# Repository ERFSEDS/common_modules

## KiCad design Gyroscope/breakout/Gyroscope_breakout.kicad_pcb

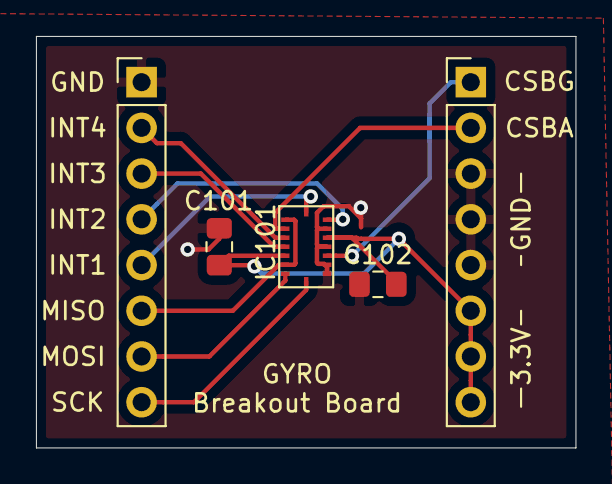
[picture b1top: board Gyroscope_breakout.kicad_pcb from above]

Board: 2 copper layers, 30.0 x 22.9 mm, 5 parts (0 on the bottom side), 11 nets.

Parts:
C101, C102: 100nF; C_0805_2012Metric_Pad1.15x1.40mm_HandSolder
IC101: BMI088; 16-LGA-(4.5x3)
J101: Conn_01x08; PinHeader_1x08_P2.54mm_Vertical
e101: Conn_01x08; PinHeader_1x08_P2.54mm_Vertical

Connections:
+3V3: C101.2, C102.2, IC101.3, IC101.11, e101.6, e101.7, e101.8
/CSB_ACCEL: IC101.14, e101.2
/CSB_GYRO: IC101.5, e101.1
/INT1_ACCEL: IC101.16, J101.5
/INT2_ACCEL: IC101.1, J101.4
/INT3_GYRO: IC101.12, J101.3
/INT4_GYRO: IC101.13, J101.2
/MISO: IC101.10, IC101.15, J101.6
/MOSI: IC101.9, J101.7
/SCK: IC101.8, J101.8
GND: C101.1, C102.1, IC101.2, IC101.4, IC101.6, IC101.7, J101.1, e101.3, e101.4, e101.5

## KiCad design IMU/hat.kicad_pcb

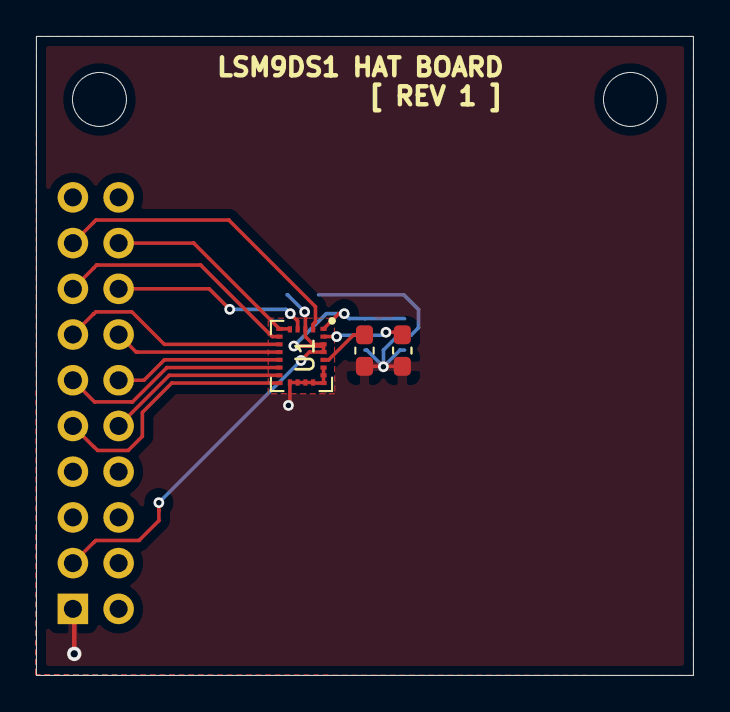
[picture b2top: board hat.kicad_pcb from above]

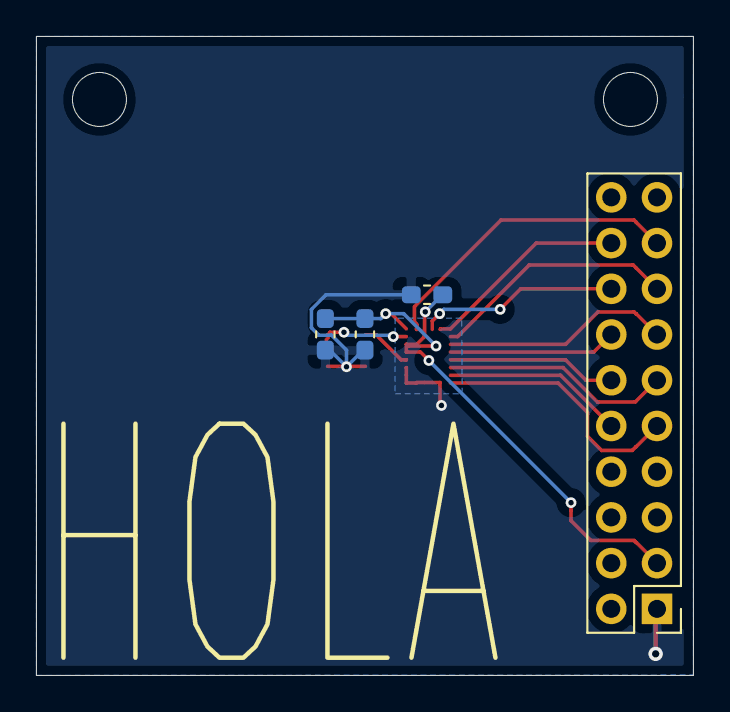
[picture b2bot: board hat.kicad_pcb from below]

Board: 2 copper layers, 36.5 x 35.5 mm, 9 parts (4 on the bottom side), 14 nets.

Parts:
C1: 10nF; C_0603_1608Metric_Pad1.05x0.95mm_HandSolder
C2, C3, C4: 100nF; C_0603_1608Metric_Pad1.05x0.95mm_HandSolder
C5: 10uF; C_0603_1608Metric_Pad1.05x0.95mm_HandSolder
H1, H3: MountingHole; MountingHole_3mm
J1: Conn_02x10_Odd_Even; PinHeader_2x10_P2.54mm_Vertical
U1: LSM9DS1; LGA-24L_3x3.5mm_P0.43mm

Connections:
+3V3: C2.1, C4.1, C5.1, J1.3, U1.1, U1.3, U1.22, U1.23
/CS: J1.15, U1.7
/CSM: J1.13, U1.8
/DEN: J1.9, U1.13
/DRDYM: J1.14, U1.9
/INT1: J1.11, U1.11
/INT2: J1.10, U1.12
/INTM: J1.12, U1.10
/MISO: J1.18, U1.5, U1.6
/MOSI: J1.16, U1.4
/SCLK: J1.17, U1.2
GND: C1.2, C2.2, C3.2, C4.2, C5.2, J1.1, U1.14, U1.15, U1.16, U1.17, U1.18, U1.19, U1.20
unnamed: C1.1, U1.21
unnamed: C3.1, U1.24

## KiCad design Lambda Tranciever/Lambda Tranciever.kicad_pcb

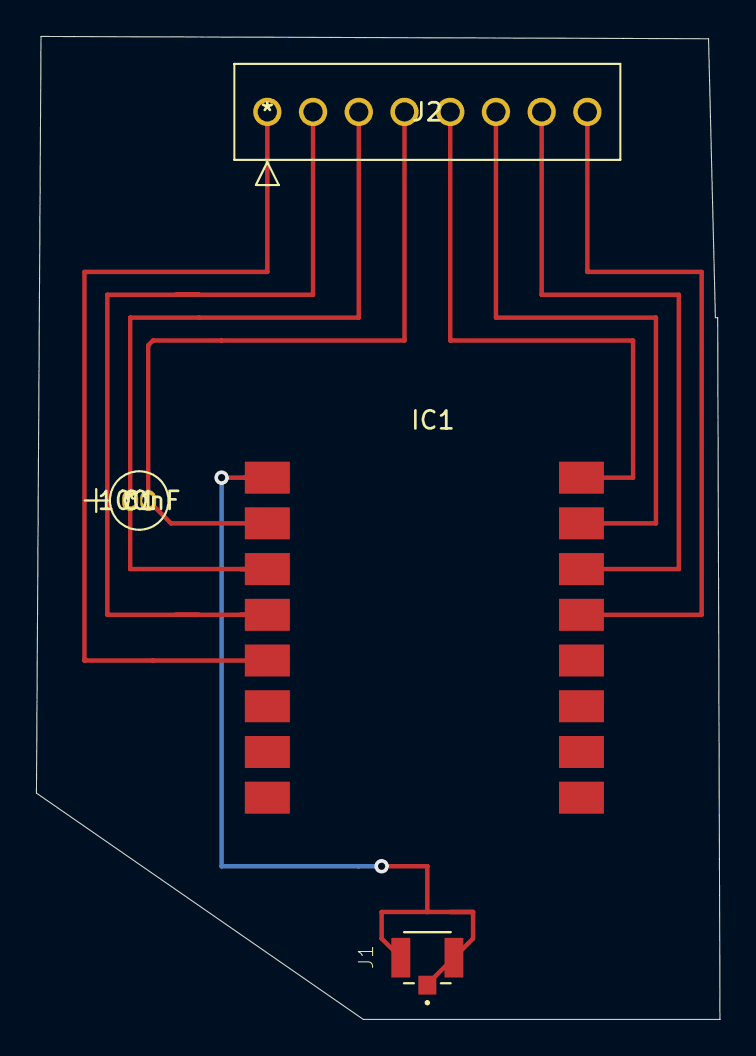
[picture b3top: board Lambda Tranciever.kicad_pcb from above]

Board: 2 copper layers, 38.0 x 54.6 mm, 4 parts (0 on the bottom side), 9 nets.

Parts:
C1: 100nF; UMA1H0R1MCD2TP
IC1: LAMBDA-9S
J1: U.FL-R-SMT(10); HRS_U.FL-R-SMT(10)
J2: PPTC081LFBN-RC

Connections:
+3V3: C1.1, IC1.3, J2.3
/12(RX2): IC1.5, J2.1
/13(TX2): IC1.4, J2.2
/19(SS): IC1.16, J2.5
/20(SCK): IC1.13, J2.8
/21(MOSI): IC1.15, J2.6
/22(MISO): IC1.14, J2.7
GND: C1.2, IC1.2, J2.4
unnamed: IC1.1, J1.1, J1.2, J1.3

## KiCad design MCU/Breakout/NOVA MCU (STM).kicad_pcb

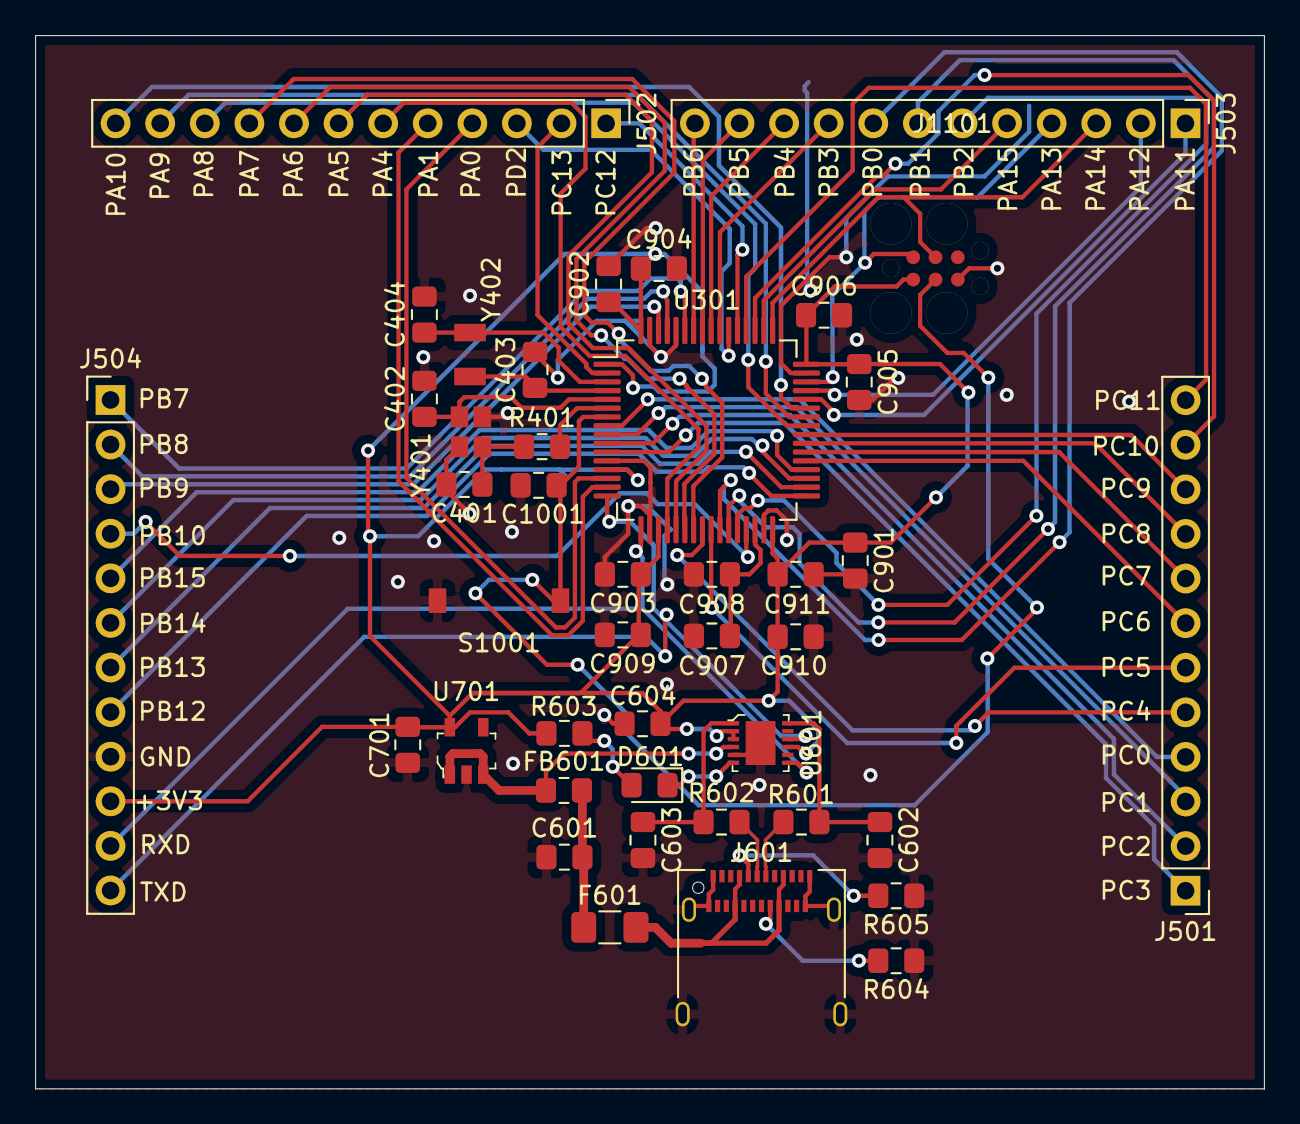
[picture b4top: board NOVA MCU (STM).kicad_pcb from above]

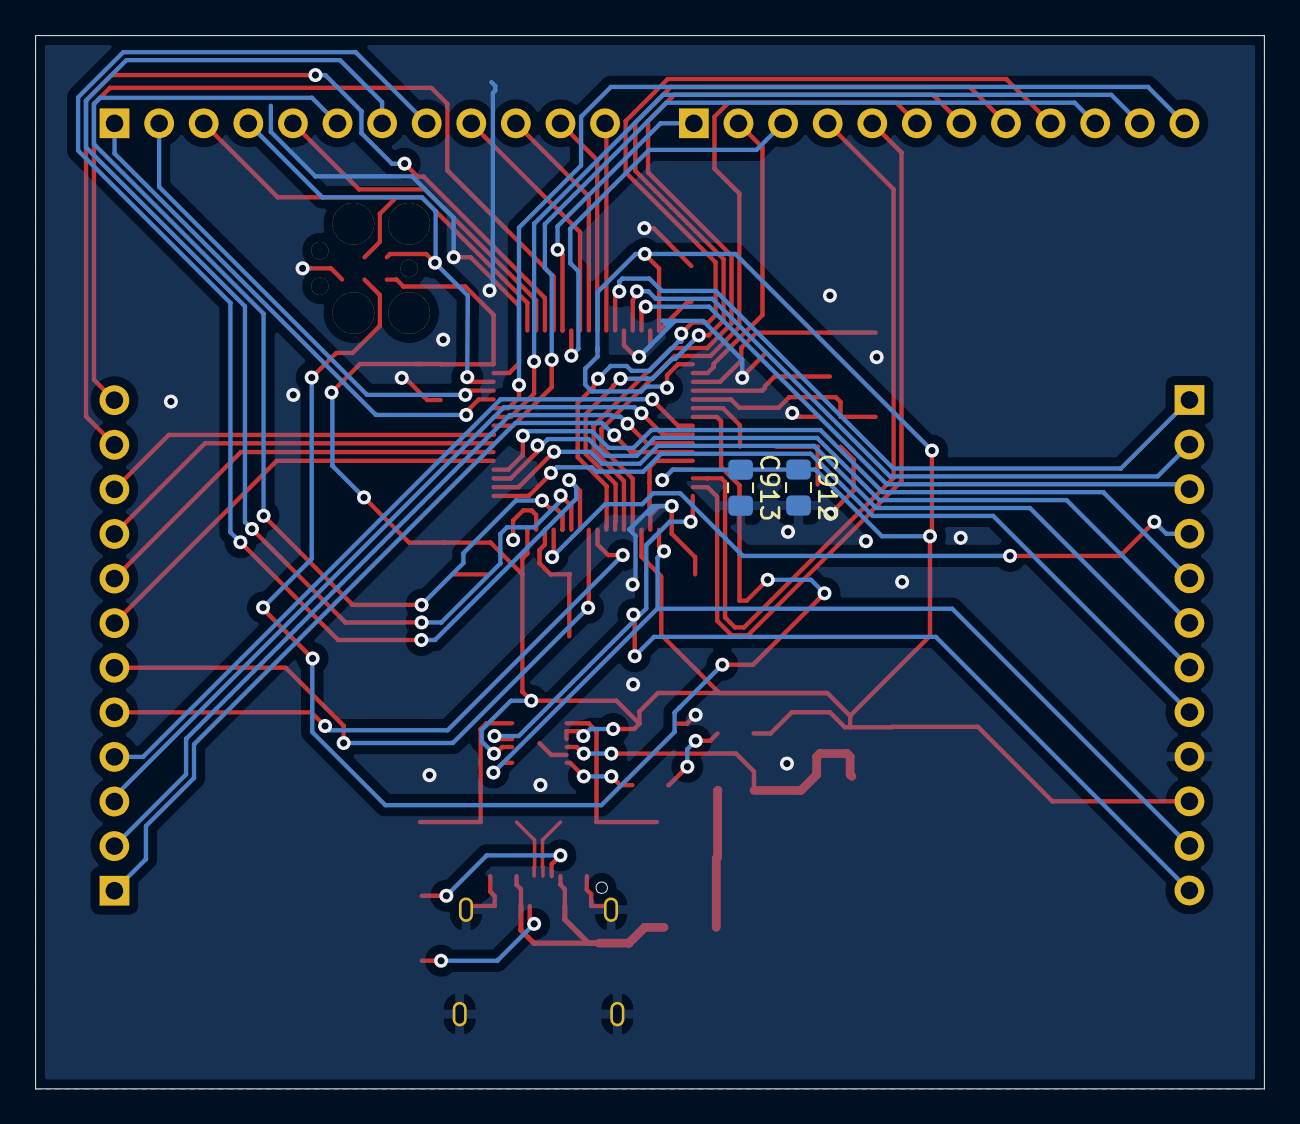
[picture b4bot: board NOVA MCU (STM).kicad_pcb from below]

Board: 2 copper layers, 70.0 x 60.0 mm, 44 parts (2 on the bottom side), 66 nets.

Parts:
C401, C402: 6pF; C_0805_2012Metric_Pad1.15x1.40mm_HandSolder
C403, C404: 2pF; C_0805_2012Metric_Pad1.15x1.40mm_HandSolder
C601: 10nF; C_0805_2012Metric_Pad1.15x1.40mm_HandSolder
C602, C603: 47pF; C_0805_2012Metric_Pad1.15x1.40mm_HandSolder
C604, C901, C902, C903, C904, C905, C906, C910, C912: 100nF; C_0805_2012Metric_Pad1.15x1.40mm_HandSolder
C701, C911, C913: 1uF; C_0805_2012Metric_Pad1.15x1.40mm_HandSolder
C907, C908: 2.2uF; C_0805_2012Metric_Pad1.15x1.40mm_HandSolder
C909: 4.7uF; C_0805_2012Metric_Pad1.15x1.40mm_HandSolder
C1001: 0.1uF; C_0805_2012Metric_Pad1.15x1.40mm_HandSolder
D601: LED; LED_0805_2012Metric_Pad1.15x1.40mm_HandSolder
F601: 500mA; Fuse_1206_3216Metric_Pad1.42x1.75mm_HandSolder
FB601: 600 OHM; R_0805_2012Metric_Pad1.15x1.40mm_HandSolder
J501, J502, J503, J504: Conn_01x12_Male; PinHeader_1x12_P2.54mm_Vertical
J601: USB_C_Receptacle; USB_C_Receptacle_Amphenol_12401610E4-2A
J1101: Conn_01x06_Male; j-link_6_pin_needle
R401: TBD; R_0805_2012Metric_Pad1.15x1.40mm_HandSolder
R601, R602: 27 OHM; R_0805_2012Metric_Pad1.15x1.40mm_HandSolder
R603: 270 OHM; R_0805_2012Metric_Pad1.15x1.40mm_HandSolder
R604, R605: 5K; R_0805_2012Metric_Pad1.15x1.40mm_HandSolder
S1001: KSR223GLFG
U301: STM32F401RBTx; LQFP-64_10x10mm_P0.5mm
U601: FT234XD-R; DFN-12-1EP_3x3mm
U701: MIC5219-3_3YM5-TR; SOT-753
Y401: ECS-260-8-36B-CKY-TR; ECX-2236B
Y402: JTX310

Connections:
+3V3: C604.1, C701.1, C901.1, C902.1, C903.1, C904.1, C905.1, C906.1, C909.1, C910.1, C911.1, C912.1, C913.1, J504.10, J1101.1, R603.2, U301.1, U301.13, U301.19, U301.32, U301.48, U301.64, U601.2, U601.3, U601.9, U701.5
/STM32F401RBT6/Clocks/CLOCKIN: C402.1, U301.5, Y401.3
/STM32F401RBT6/Clocks/CLOCKOUT: R401.2, U301.6
/STM32F401RBT6/Clocks/RTCCRYSTALIN: C404.1, U301.3, Y402.2
/STM32F401RBT6/Clocks/RTCCRYSTALOUT: C403.1, U301.4, Y402.1
/STM32F401RBT6/FILTERING/VCAP: C907.2, C908.2, U301.30
/STM32F401RBT6/MCU/RESET: C1001.1, J1101.3, S1001.2, U301.7
/STM32F401RBT6/Pin Headers/1: J501.4, U301.8
/STM32F401RBT6/Pin Headers/2: J501.3, U301.9
/STM32F401RBT6/Pin Headers/3: J501.2, U301.10
/STM32F401RBT6/Pin Headers/4: J501.1, U301.11
/STM32F401RBT6/Pin Headers/5: J501.5, U301.24
/STM32F401RBT6/Pin Headers/6: J501.6, U301.25
/STM32F401RBT6/Pin Headers/7: J501.7, U301.37
/STM32F401RBT6/Pin Headers/8: J501.8, U301.38
/STM32F401RBT6/Pin Headers/9: J501.9, U301.39
/STM32F401RBT6/Pin Headers/10: J501.10, U301.40
/STM32F401RBT6/Pin Headers/11: J501.11, U301.51
/STM32F401RBT6/Pin Headers/12: J501.12, U301.52
/STM32F401RBT6/Pin Headers/13: J502.1, U301.53
/STM32F401RBT6/Pin Headers/14: J502.2, U301.2
/STM32F401RBT6/Pin Headers/15: J502.3, U301.54
/STM32F401RBT6/Pin Headers/16: J502.4, U301.14
/STM32F401RBT6/Pin Headers/17: J502.5, U301.15
/STM32F401RBT6/Pin Headers/18: J502.6, U301.20
/STM32F401RBT6/Pin Headers/19: J502.7, U301.21
/STM32F401RBT6/Pin Headers/20: J502.8, U301.22
/STM32F401RBT6/Pin Headers/21: J502.9, U301.23
/STM32F401RBT6/Pin Headers/22: J502.10, U301.41
/STM32F401RBT6/Pin Headers/23: J502.11, U301.42
/STM32F401RBT6/Pin Headers/24: J502.12, U301.43
/STM32F401RBT6/Pin Headers/25: J503.1, U301.44
/STM32F401RBT6/Pin Headers/26: J503.2, U301.45
/STM32F401RBT6/Pin Headers/29: J503.5, U301.50
/STM32F401RBT6/Pin Headers/30: J503.8, U301.26
/STM32F401RBT6/Pin Headers/31: J503.7, U301.27
/STM32F401RBT6/Pin Headers/32: J503.6, U301.28
/STM32F401RBT6/Pin Headers/33: J503.9, U301.55
/STM32F401RBT6/Pin Headers/34: J503.10, U301.56
/STM32F401RBT6/Pin Headers/35: J503.11, U301.57
/STM32F401RBT6/Pin Headers/36: J503.12, U301.58
/STM32F401RBT6/Pin Headers/37: J504.1, U301.59
/STM32F401RBT6/Pin Headers/38: J504.2, U301.61
/STM32F401RBT6/Pin Headers/39: J504.3, U301.62
/STM32F401RBT6/Pin Headers/40: J504.4, U301.29
/STM32F401RBT6/Pin Headers/41: J504.8, U301.33
/STM32F401RBT6/Pin Headers/42: J504.7, U301.34
/STM32F401RBT6/Pin Headers/43: J504.6, U301.35
/STM32F401RBT6/Pin Headers/44: J504.5, U301.36
/STM32F401RBT6/RXD: J504.11, U301.17, U601.7
/STM32F401RBT6/SWCLK: J503.3, J1101.4, U301.49
/STM32F401RBT6/SWDIO: J503.4, J1101.2, U301.46
/STM32F401RBT6/TXD: J504.12, U301.16, U601.10
/STM32F401RBT6/USB-C/D1+: J601.A6, R602.2
/STM32F401RBT6/USB-C/D1-: J601.A7, R601.2
/STM32F401RBT6/USB-C/D2+: C603.1, R602.1, U601.1
/STM32F401RBT6/USB-C/D2-: C602.1, R601.1, U601.12
GND: C401.2, C402.2, C403.2, C404.2, C601.1, C602.2, C603.2, C604.2, C701.2, C901.2, C902.2, C903.2, C904.2, C905.2, C906.2, C907.1, C908.1, C909.2, C910.2, C911.2, C912.2, C913.2, C1001.2, J504.9, J601.A1, J601.A12, J601.B1, J601.B12, J601.S1, J1101.5, R604.1, R605.1, S1001.1, U301.12, U301.18, U301.31, U301.47, U301.60, U301.63, U601.5, U601.13, U701.2, Y401.2, Y401.4
unnamed: C401.1, R401.1, Y401.1
unnamed: C601.2, F601.1, FB601.2
unnamed: D601.1, U601.6
unnamed: D601.2, R603.1
unnamed: F601.2, J601.A4, J601.A9, J601.B4, J601.B9
unnamed: J601.A5, R605.2
unnamed: J601.B5, R604.2
VBUS: FB601.1, U601.4, U701.1, U701.3

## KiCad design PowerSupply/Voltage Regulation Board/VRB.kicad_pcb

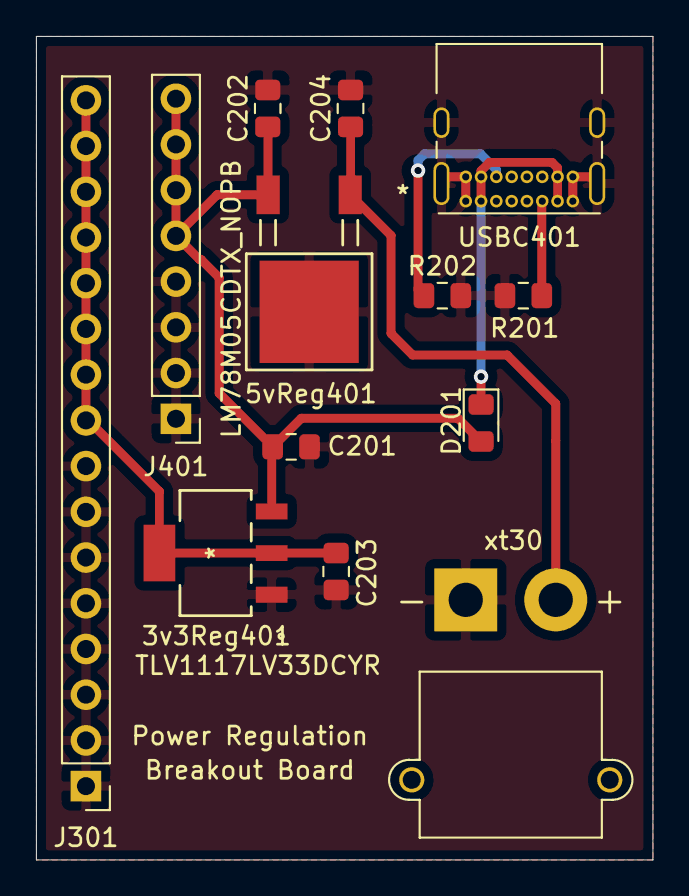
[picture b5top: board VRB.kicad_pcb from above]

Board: 2 copper layers, 34.2 x 45.8 mm, 13 parts (0 on the bottom side), 7 nets.

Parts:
3v3Reg401: TLV1117LV33DCYR
5vReg401: LM78M05CDTX_NOPB; LM78M05CDTX&slash_NOPB
C201: 0.33 uF; C_0805_2012Metric_Pad1.15x1.40mm_HandSolder
C202, C204: 1 uF; C_0805_2012Metric_Pad1.15x1.40mm_HandSolder
C203: 0.1 uF; C_0805_2012Metric_Pad1.15x1.40mm_HandSolder
D201: DIODE; D_0805_2012Metric_Pad1.15x1.40mm_HandSolder
J301: 16PinConnector; PinHeader_1x16_P2.54mm_Vertical
J401: 8PinConnector; PinHeader_1x08_P2.54mm_Vertical
R201, R202: 5k; R_0805_2012Metric_Pad1.15x1.40mm_HandSolder
USBC401: USB_C_2.0; USB_C_Receptacle_GCT_USB4085
xt30: Conn_01x02; AMASS_XT30PW-M_1x02_P2.50mm_Horizontal

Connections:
+3V3: 3v3Reg401.2, 3v3Reg401.4, C203.2, J301.9, J301.10, J301.11, J301.12, J301.13, J301.14, J301.15, J301.16
+5V: 3v3Reg401.3, 5vReg401.3, C201.1, C202.1, D201.2, J401.5, J401.6, J401.7, J401.8
GND: 3v3Reg401.1, 5vReg401.2, C201.2, C202.2, C203.1, C204.2, J301.1, J301.2, J301.3, J301.4, J301.5, J301.6, J301.7, J301.8, J401.1, J401.2, J401.3, J401.4, R201.1, R202.2, USBC401.A1, USBC401.A12, USBC401.B1, USBC401.B12, USBC401.S1, xt30.1
unnamed: 5vReg401.1, C204.1, xt30.2
unnamed: D201.1, USBC401.A4, USBC401.A9, USBC401.B4, USBC401.B9
unnamed: R201.2, USBC401.A5
unnamed: R202.1, USBC401.B5

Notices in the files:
parts and their libraries:
Copyright 2021 Accelerated Designs. All rights reserved.
Copyright 2016 Accelerated Designs. All rights reserved.
